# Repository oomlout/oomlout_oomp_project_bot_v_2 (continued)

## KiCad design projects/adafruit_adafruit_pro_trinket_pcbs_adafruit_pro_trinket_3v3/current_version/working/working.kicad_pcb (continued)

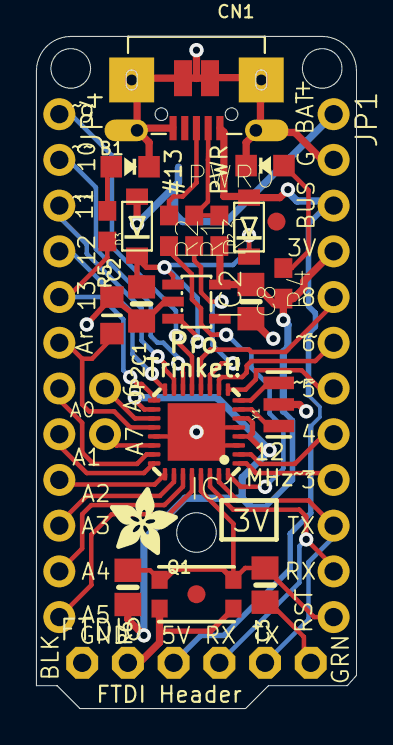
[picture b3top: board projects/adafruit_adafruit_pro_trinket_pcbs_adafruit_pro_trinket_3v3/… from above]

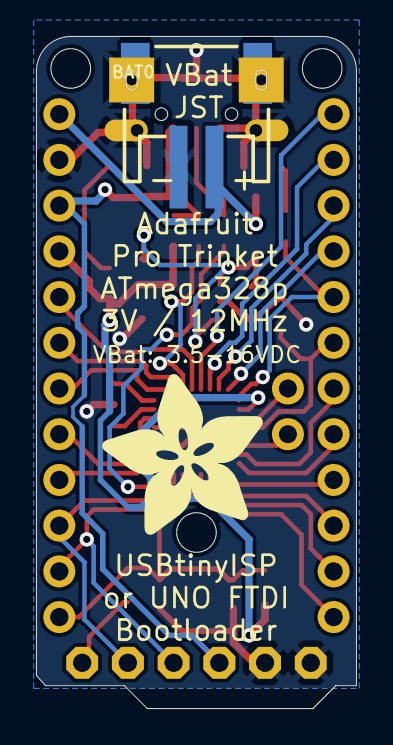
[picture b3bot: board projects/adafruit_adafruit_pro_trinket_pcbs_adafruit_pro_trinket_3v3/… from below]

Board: 16 copper layers, 17.8 x 37.3 mm, 31 parts (2 on the bottom side), 36 nets.

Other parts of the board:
@HOLE0, @HOLE1, @HOLE2: (no value)
U$7: ADAFRUIT_3.5MM
U$9: ADAFRUIT_9MM

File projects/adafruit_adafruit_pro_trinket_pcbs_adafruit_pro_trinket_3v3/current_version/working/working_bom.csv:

"Id";"Designator";"Footprint";"Quantity";"Designation";"Supplier and ref";
1;"IC2";"SOT23-5L";1;"MIC5225-3.3v";;;
2;"D2,D3";"SOD-123FL";2;"SCHOTTKY";;;
3;"JP2";"1X02_ROUND";1;"";;;
4;"@HOLE1,@HOLE2,@HOLE0";"";3;"";;;
5;"IC1";"MLF32-TH";1;"ATmega328P";;;
6;"U$1,U$6";"FIDUCIAL_1MM";2;"FIDUCIAL";;;
7;"C2";"_0805MP";1;"0.1uF";;;
8;"CN1";"4UCONN_20329";1;"";;;
9;"R3";"0603-NO";1;"1.5K (0603)";;;
10;"R4,R5";"0603-NO";2;"470 (0603)";;;
11;"JP4,JP1";"1X12-CB";2;"";;;
12;"Y1";"RESONATOR-SMD";1;"12MHz";;;
13;"U$7";"ADAFRUIT_3.5MM";1;"";;;
14;"C3";"0805-NO";1;"0.1uF";;;
15;"PWR0";"CHIPLED_0805_NOOUTLINE";1;"green";;;
16;"Q1";"BTN_KMR2_4.6X2.8";1;"reset";;;
17;"R1,R2";"0603-NO";2;"68 (0603)";;;
18;"C1,C8";"0805-NO";2;"10uF";;;
19;"B1";"CHIPLED_0805_NOOUTLINE";1;"red";;;
20;"R6";"0805-NO";1;"10K (0603)";;;
21;"FTDI0";"1X06-CLEANBIG";1;"";;;
22;"U$9";"ADAFRUIT_9MM";1;"";;;
23;"BAT0";"JSTPH2";1;"";;;

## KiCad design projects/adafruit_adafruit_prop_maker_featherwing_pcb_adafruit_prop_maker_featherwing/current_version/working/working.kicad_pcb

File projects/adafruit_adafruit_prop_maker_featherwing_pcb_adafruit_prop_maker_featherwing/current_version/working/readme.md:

# adafruit_prop_maker_featherwing_pcb
 
## summary 
* id: adafruit_adafruit_prop_maker_featherwing_pcb_adafruit_prop_maker_featherwing
* user: adafruit
* name: adafruit_prop_maker_featherwing_pcb
* board: adafruit_prop_maker_featherwing
* repo: https://github.com/adafruit/Adafruit-Prop-Maker-FeatherWing-PCB

* src_file_repo_sch: 
* src_file_repo_sch_link: https://github.com/adafruit/Adafruit-Prop-Maker-FeatherWing-PCB/tree/master/
* full details link: https://github.com/oomlout/oomlout_oomp_project_bot_v_2/tree/main/projects/adafruit_adafruit_prop_maker_featherwing_pcb_adafruit_prop_maker_featherwing/current_version/working  

## schematic  
  
[schematic (pdf)](working_schematic.pdf) 

## pcb  

[board (pdf)](working.pdf)  

## working_bom
| Id | Designator | Footprint | Quantity | Designation | Supplier and ref |  | None | 
| --- | --- | --- | --- | --- | --- | --- | --- | 
| 1 | R4,R1,R6,R5 | 0603-NO | 4 | 100k |  |  | [''] | 
| 2 | C1,C15,C2,C3 | 0805-NO | 4 | 10uF |  |  | [''] | 
| 3 | R9,R8 | _1206 | 2 | 1.75o |  |  | [''] | 
| 4 | VR2 | TRIMPOT_BOURNS_3303W | 1 | 10K trim |  |  | [''] | 
| 5 | JP4 | 1X16_ROUND | 1 |  |  |  | [''] | 
| 6 | R2,R3 | 0603-NO | 2 | 10K |  |  | [''] | 
| 7 | R11 | 0603-NO | 1 | 100K |  |  | [''] | 
| 8 | C9,C4,C13 | 0603-NO | 3 | 1uF |  |  | [''] | 
| 9 | FID1,FID3 | FIDUCIAL_1MM | 2 | FIDUCIAL_1MM |  |  | [''] | 
| 10 | Q4,Q2,Q6,Q5 | SOT23-WIDE | 4 | DMG3406 |  |  | [''] | 
| 11 | D2,D1 | SOD-123 | 2 | MBR120 |  |  | [''] | 
| 12 | R12,R13 | 0603-NO | 2 | 100 |  |  | [''] | 
| 13 | U$14 | PROPMAKER_TOP | 1 |  |  |  | [''] | 
| 14 | X6 | JSTPH2 | 1 | CON_JST_PH_2PIN_MTPH2 |  |  | [''] | 
| 15 | @HOLE0,@HOLE2,@HOLE1 |  | 3 |  |  |  | [''] | 
| 16 | NEO0 | JSTPH3 | 1 | JST PH 3 |  |  | [''] | 
| 17 | JP2,EN_PINS0 | 1X02_ROUND | 2 |  |  |  | [''] | 
| 18 | U5 | MSOP8_0.65MM | 1 | PAM8302AASCR |  |  | [''] | 
| 19 | SW1 | BTN_KMR2_4.6X2.8 | 1 | KMR2 |  |  | [''] | 
| 20 | IC4 | LGA16_3X3MM | 1 | LIS3DH |  |  | [''] | 
| 21 | U$1 | 53398-0271 | 1 | CON_MOLEX_2P |  |  | [''] | 
| 22 | JP1 | 1X12_ROUND | 1 |  |  |  | [''] | 
| 23 | IC2 | SOT23-5 | 1 | 74AHCT1G125DBV |  |  | [''] | 
| 24 | R7 | _1206 | 1 | 3o |  |  | [''] | 
| 25 | JP5 | 1X04_ROUND | 1 |  |  |  | [''] | 
| 26 | MS1 | FEATHERWING | 1 | FEATHERWING |  |  | [''] | 
| 27 | Q3 | SOT23-WIDE | 1 | DMG3415U-7 |  |  | [''] | 
| 28 | U$15 | PCBFEAT-REV-040 | 1 |  |  |  | [''] | 
| 29 | U$6 | PROPMAKER_BOT | 1 |  |  |  | [''] | 

## bom_schematic
| Ref | Qnty | Value | Cmp name | Footprint | Description | Vendor | DNP | 
| --- | --- | --- | --- | --- | --- | --- | --- | 
| C1, C2, C3, C15 | 4 | 10uF | CAP_CERAMIC0805-NOOUTLINE | working:0805-NO |  |  |  | 
| C4, C9, C13 | 3 | 1uF | CAP_CERAMIC0603_NO | working:0603-NO |  |  |  | 
| D1, D2 | 2 | MBR120 | DIODE-SCHOTTKYSOD-123 | working:SOD-123 |  |  |  | 
| EN_PINS0 | 1 | HEADER-1X2ROUND | HEADER-1X2ROUND | working:1X02_ROUND |  |  |  | 
| FID1, FID3 | 2 | FIDUCIAL_1MM | FIDUCIAL_1MM | working:FIDUCIAL_1MM |  |  |  | 
| IC2 | 1 | 741G125DBV | 741G125DBV | working:SOT23-5 |  |  |  | 
| IC4 | 1 | LIS3DH | ACCEL_LIS3DHTR | working:LGA16_3X3MM |  |  |  | 
| JP1 | 1 | HEADER-1X12 | HEADER-1X12 | working:1X12_ROUND |  |  |  | 
| JP2 | 1 | HEADER-1X2ROUND | HEADER-1X2ROUND | working:1X02_ROUND |  |  |  | 
| JP4 | 1 | HEADER-1X16ROUND | HEADER-1X16ROUND | working:1X16_ROUND |  |  |  | 
| JP5 | 1 | HEADER-1X4ROUND | HEADER-1X4ROUND | working:1X04_ROUND |  |  |  | 
| MS1 | 1 | FEATHERWING | FEATHERWING | working:FEATHERWING |  |  |  | 
| NEO0 | 1 | JST PH 3 | CON_JST_PH_3PIN | working:JSTPH3 |  |  |  | 
| Q2, Q4, Q5, Q6 | 4 | DMG3406 | MOSFET-NWIDE | working:SOT23-WIDE |  |  |  | 
| Q3 | 1 | DMG3415U-7 | MOSFET-PWIDE | working:SOT23-WIDE |  |  |  | 
| R1, R4, R5, R6 | 4 | 100k | RESISTOR_0603_NOOUT | working:0603-NO |  |  |  | 
| R2, R3 | 2 | 10K | RESISTOR_0603_NOOUT | working:0603-NO |  |  |  | 
| R7 | 1 | 3o | RESISTOR_1206 | working:_1206 |  |  |  | 
| R8, R9 | 2 | 1.75o | RESISTOR_1206 | working:_1206 |  |  |  | 
| R11 | 1 | 100K | RESISTOR_0603_NOOUT | working:0603-NO |  |  |  | 
| R12, R13 | 2 | 100 | RESISTOR_0603_NOOUT | working:0603-NO |  |  |  | 
| SW1 | 1 | KMR2 | SWITCH_TACT_SMT4.6X2.8 | working:BTN_KMR2_4.6X2.8 |  |  |  | 
| U5 | 1 | PAM8302AASCR | AUDIOAMP_PAM8302A | working:MSOP8_0.65MM |  |  |  | 
| U$1 | 1 | CON_MOLEX_2P | CON_MOLEX_2P | working:53398-0271 |  |  |  | 
| VR2 | 1 | 10K trim | TRIMPOT3303W/X | working:TRIMPOT_BOURNS_3303W |  |  |  | 
| X6 | 1 | CON_JST_PH_2PIN_MTPH2 | CON_JST_PH_2PIN_MTPH2 | working:JSTPH2 |  |  |  |

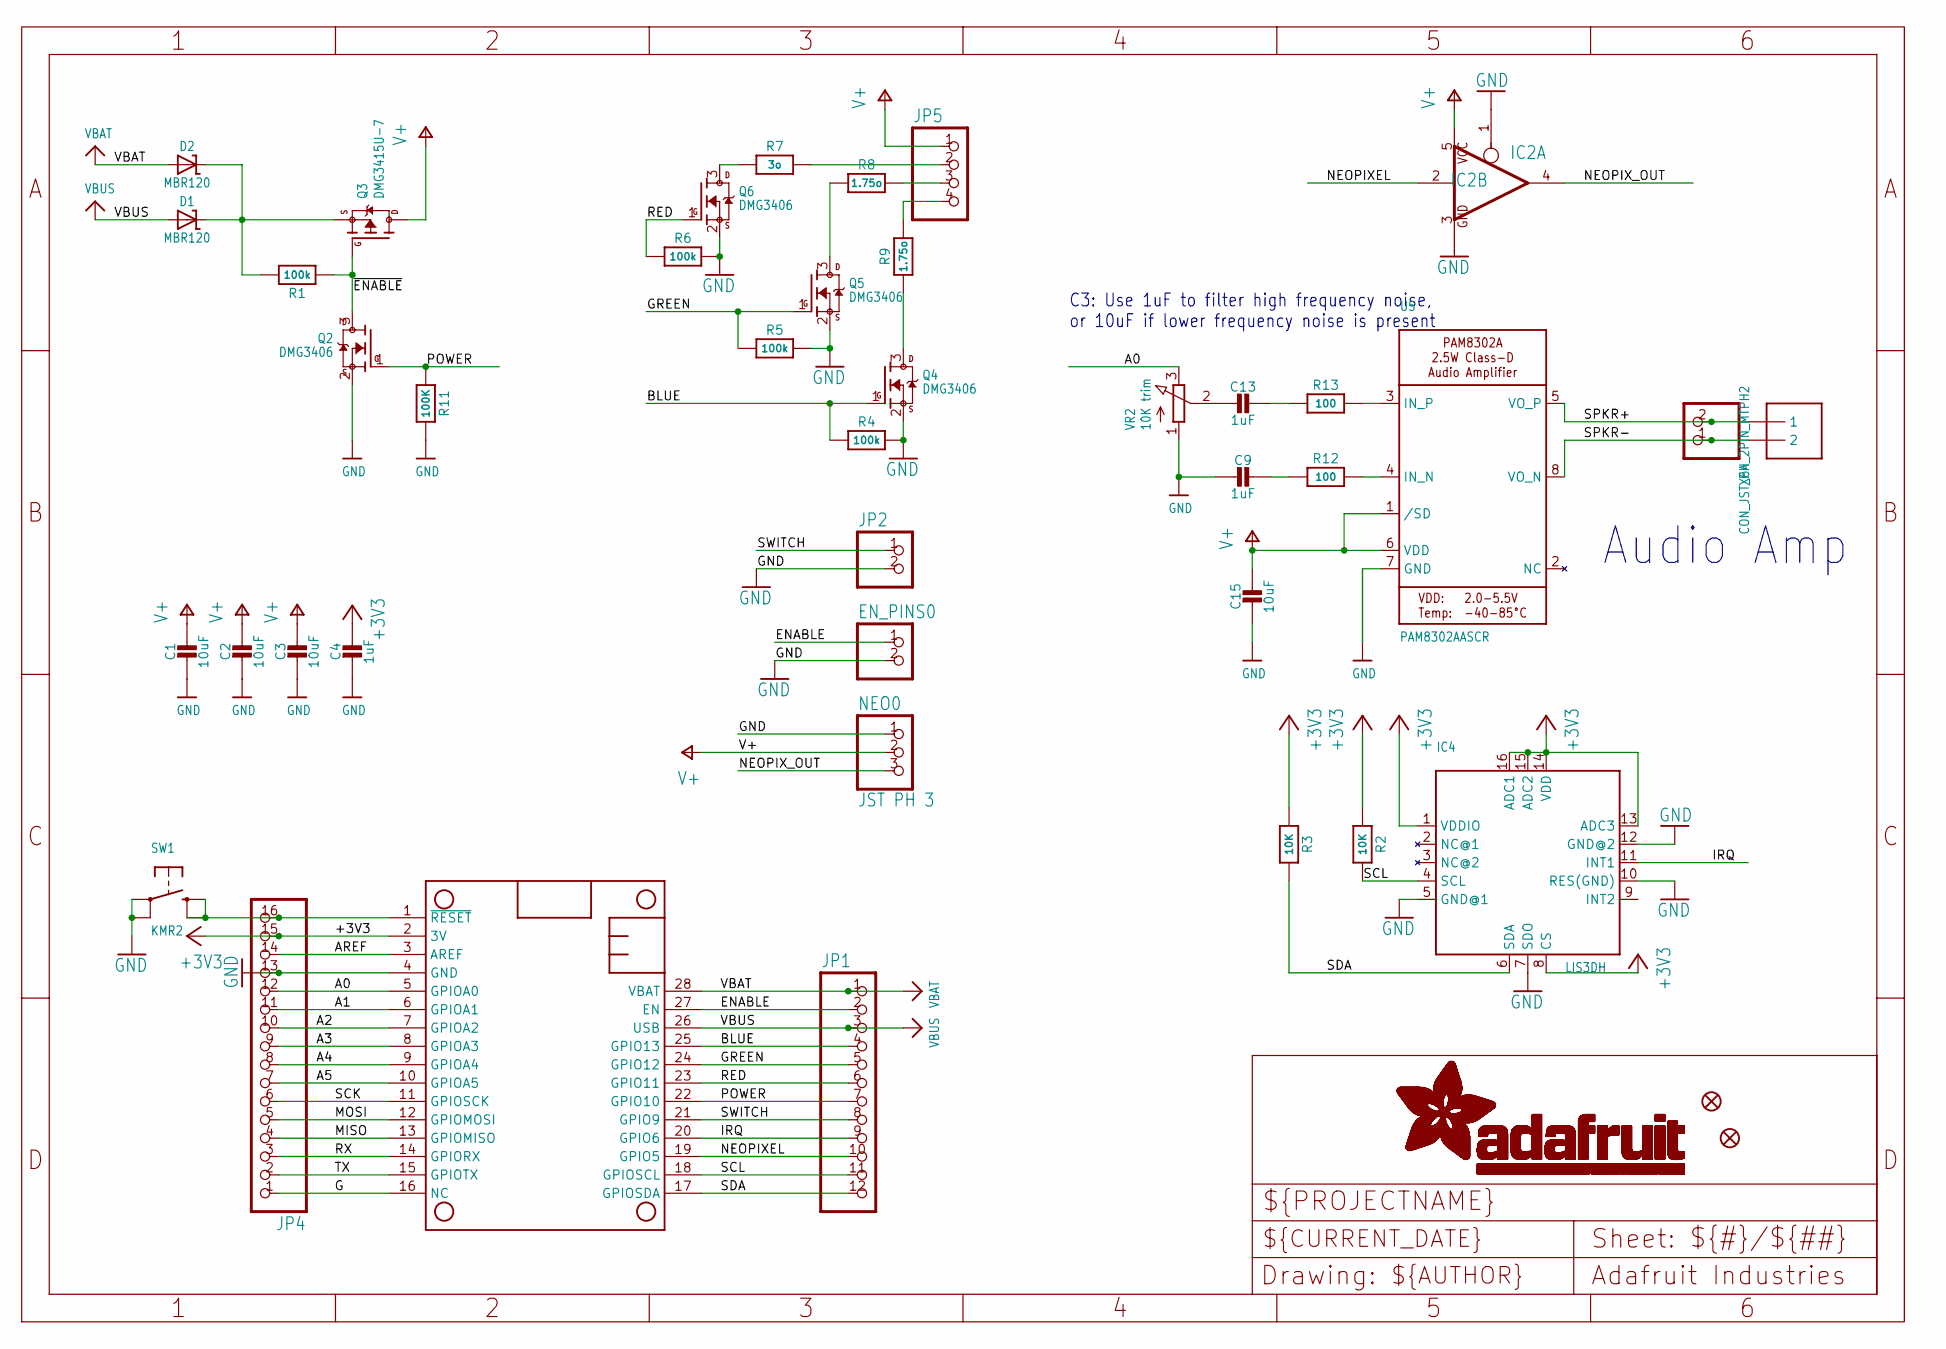
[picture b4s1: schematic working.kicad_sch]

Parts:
C1, C2, C3, C15: 10uF; 0805-NO
C4, C9, C13: 1uF; 0603-NO
D1, D2: MBR120; SOD-123
EN_PINS0: HEADER-1X2ROUND; 1X02_ROUND
FID1, FID3: FIDUCIAL_1MM
IC2: 741G125DBV; SOT23-5
IC4: LIS3DH; LGA16_3X3MM
JP1: HEADER-1X12; 1X12_ROUND
JP2: HEADER-1X2ROUND; 1X02_ROUND
JP4: HEADER-1X16ROUND; 1X16_ROUND
JP5: HEADER-1X4ROUND; 1X04_ROUND
MS1: FEATHERWING
NEO0: JST PH 3; JSTPH3
Q2, Q4, Q5, Q6: DMG3406; SOT23-WIDE
Q3: DMG3415U-7; SOT23-WIDE
R1, R4, R5, R6: 100k; 0603-NO
R2, R3: 10K; 0603-NO
R7: 3o; _1206
R8, R9: 1.75o; _1206
R11: 100K; 0603-NO
R12, R13: 100; 0603-NO
SW1: KMR2; BTN_KMR2_4.6X2.8
U5: PAM8302AASCR; MSOP8_0.65MM
U$1: CON_MOLEX_2P; 53398-0271
VR2: 10K trim; TRIMPOT_BOURNS_3303W
X6: CON_JST_PH_2PIN_MTPH2; JSTPH2

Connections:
+3V3: C4.1, IC4.1 (VDDIO), IC4.8 (CS), IC4.13 (ADC3), IC4.14 (VDD), IC4.15 (ADC2), IC4.16 (ADC1), JP4.15, MS1.2 (3V), R2.1, R3.1
A0: JP4.12, MS1.5 (GPIOA0), VR2.3 (E)
A1: JP4.11, MS1.6 (GPIOA1)
A2: JP4.10, MS1.7 (GPIOA2)
A3: JP4.9, MS1.8 (GPIOA3)
A4: JP4.8, MS1.9 (GPIOA4)
A5: JP4.7, MS1.10 (GPIOA5)
AREF: JP4.14, MS1.3 (AREF)
BLUE: JP1.4, MS1.25 (GPIO13), Q4.1 (G), R4.1
ENABLE: EN_PINS0.1, JP1.2, MS1.27 (EN)
G: JP4.1, MS1.16 (NC)
GND: C1.2, C2.2, C3.2, C4.2, C9.2, C15.2, EN_PINS0.2, IC2.1 (OE), IC2.3 (GND), IC4.5 (GND@1), IC4.7 (SDO), IC4.10 (RES(GND)), IC4.12 (GND@2), JP2.2, JP4.13, MS1.4 (GND), NEO0.1, Q2.2 (S), Q4.2 (S), Q5.2 (S), Q6.2 (S), R4.2, R5.2, R6.2, R11.2, SW1.A, SW1.A' (P1), U5.7 (GND), VR2.1 (A)
GREEN: JP1.5, MS1.24 (GPIO12), Q5.1 (G), R5.1
IRQ: IC4.11 (INT1), JP1.9, MS1.20 (GPIO6)
MISO: JP4.4, MS1.13 (GPIOMISO)
MOSI: JP4.5, MS1.12 (GPIOMOSI)
unnamed: Q6.3 (D), R7.1
unnamed: JP5.3, R8.2
unnamed: JP5.4, R9.2
unnamed: Q4.3 (D), R9.1
unnamed: Q5.3 (D), R8.1
unnamed: JP5.2, R7.2
unnamed: R12.2, U5.4 (IN_N)
unnamed: R13.2, U5.3 (IN_P)
unnamed: C9.1, R12.1
unnamed: C13.1, R13.1
unnamed: C13.2, VR2.2 (S)
unnamed: D1.C, D2.C, Q3.2 (S), R1.2
NEOPIXEL: IC2.2 (I), JP1.10, MS1.19 (GPIO5)
NEOPIX_OUT: IC2.4 (O), NEO0.3
POWER: JP1.7, MS1.22 (GPIO10), Q2.1 (G), R11.1
RED: JP1.6, MS1.23 (GPIO11), Q6.1 (G), R6.1
RESET: JP4.16, MS1.1 (~RESET), SW1.B (S), SW1.B' (S1)
RX: JP4.3, MS1.14 (GPIORX)
SCK: JP4.6, MS1.11 (GPIOSCK)
SCL: IC4.4 (SCL), JP1.11, MS1.18 (GPIOSCL), R2.2
SDA: IC4.6 (SDA), JP1.12, MS1.17 (GPIOSDA), R3.2
SPKR+: U5.5 (VO_P), U$1.1, X6.2
SPKR-: U5.8 (VO_N), U$1.2, X6.1
SWITCH: JP1.8, JP2.1, MS1.21 (GPIO9)
TX: JP4.2, MS1.15 (GPIOTX)
V+: C1.1, C2.1, C3.1, C15.1, IC2.5 (VCC), JP5.1, NEO0.2, Q3.3 (D), U5.1 (/SD), U5.6 (VDD)
VBAT: D2.A, JP1.1, MS1.28 (VBAT)
VBUS: D1.A, JP1.3, MS1.26 (USB)
~ENABLE: Q2.3 (D), Q3.1 (G), R1.1

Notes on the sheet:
C3: Use 1uF to filter high frequency noise, or 10uF if lower frequency noise is present
Audio Amp

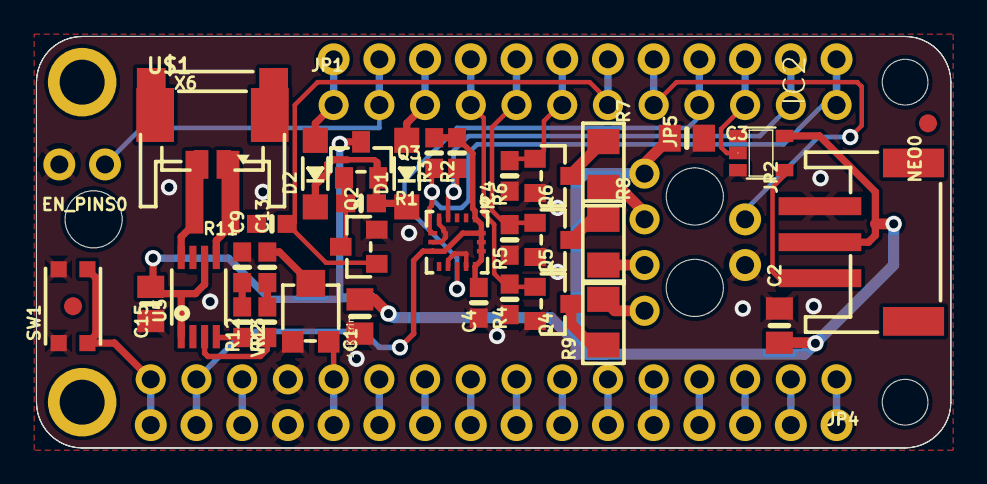
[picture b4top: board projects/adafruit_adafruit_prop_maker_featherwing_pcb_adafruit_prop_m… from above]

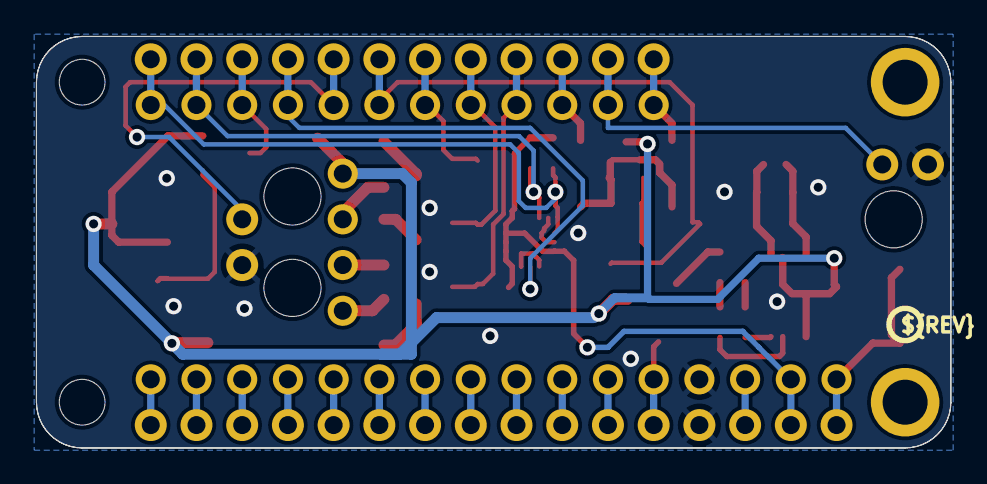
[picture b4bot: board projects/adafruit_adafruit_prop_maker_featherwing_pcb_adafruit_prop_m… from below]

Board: 2 copper layers, 50.8 x 22.9 mm, 48 parts (2 on the bottom side), 45 nets.

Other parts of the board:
@HOLE0, @HOLE1, @HOLE2: (no value)
U$6: PROPMAKER_BOT
U$14: PROPMAKER_TOP
U$15: PCBFEAT-REV-040

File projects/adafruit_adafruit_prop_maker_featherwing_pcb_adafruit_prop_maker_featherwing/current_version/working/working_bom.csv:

"Id";"Designator";"Footprint";"Quantity";"Designation";"Supplier and ref";
1;"R4,R1,R6,R5";"0603-NO";4;"100k";;;
2;"C1,C15,C2,C3";"0805-NO";4;"10uF";;;
3;"R9,R8";"_1206";2;"1.75o";;;
4;"VR2";"TRIMPOT_BOURNS_3303W";1;"10K trim";;;
5;"JP4";"1X16_ROUND";1;"";;;
6;"R2,R3";"0603-NO";2;"10K";;;
7;"R11";"0603-NO";1;"100K";;;
8;"C9,C4,C13";"0603-NO";3;"1uF";;;
9;"FID1,FID3";"FIDUCIAL_1MM";2;"FIDUCIAL_1MM";;;
10;"Q4,Q2,Q6,Q5";"SOT23-WIDE";4;"DMG3406";;;
11;"D2,D1";"SOD-123";2;"MBR120";;;
12;"R12,R13";"0603-NO";2;"100";;;
13;"U$14";"PROPMAKER_TOP";1;"";;;
14;"X6";"JSTPH2";1;"CON_JST_PH_2PIN_MTPH2";;;
15;"@HOLE0,@HOLE2,@HOLE1";"";3;"";;;
16;"NEO0";"JSTPH3";1;"JST PH 3";;;
17;"JP2,EN_PINS0";"1X02_ROUND";2;"";;;
18;"U5";"MSOP8_0.65MM";1;"PAM8302AASCR";;;
19;"SW1";"BTN_KMR2_4.6X2.8";1;"KMR2";;;
20;"IC4";"LGA16_3X3MM";1;"LIS3DH";;;
21;"U$1";"53398-0271";1;"CON_MOLEX_2P";;;
22;"JP1";"1X12_ROUND";1;"";;;
23;"IC2";"SOT23-5";1;"74AHCT1G125DBV";;;
24;"R7";"_1206";1;"3o";;;
25;"JP5";"1X04_ROUND";1;"";;;
26;"MS1";"FEATHERWING";1;"FEATHERWING";;;
27;"Q3";"SOT23-WIDE";1;"DMG3415U-7";;;
28;"U$15";"PCBFEAT-REV-040";1;"";;;
29;"U$6";"PROPMAKER_BOT";1;"";;;

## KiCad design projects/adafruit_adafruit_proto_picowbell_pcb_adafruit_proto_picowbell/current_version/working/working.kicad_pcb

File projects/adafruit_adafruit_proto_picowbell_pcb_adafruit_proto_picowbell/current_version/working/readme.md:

# adafruit_proto_picowbell_pcb
 
## summary 
* id: adafruit_adafruit_proto_picowbell_pcb_adafruit_proto_picowbell
* user: adafruit
* name: adafruit_proto_picowbell_pcb
* board: adafruit_proto_picowbell
* repo: https://github.com/adafruit/Adafruit-Proto-PiCowbell-PCB

* src_file_repo_sch: 
* src_file_repo_sch_link: https://github.com/adafruit/Adafruit-Proto-PiCowbell-PCB/tree/main/
* full details link: https://github.com/oomlout/oomlout_oomp_project_bot_v_2/tree/main/projects/adafruit_adafruit_proto_picowbell_pcb_adafruit_proto_picowbell/current_version/working  

## schematic  
  
[schematic (pdf)](working_schematic.pdf) 

## pcb  

[board (pdf)](working.pdf)  

## working_bom
| Id | Designator | Footprint | Quantity | Designation | Supplier and ref |  | None | 
| --- | --- | --- | --- | --- | --- | --- | --- | 
| 1 | PLABEL34 | PLABEL34 | 1 |  |  |  | [''] | 
| 2 | PLABEL18 | PLABEL18 | 1 |  |  |  | [''] | 
| 3 | PLABEL20 | PLABEL20 | 1 |  |  |  | [''] | 
| 4 | PLABEL4 | PLABEL4 | 1 |  |  |  | [''] | 
| 5 | PLABEL32 | PLABEL32 | 1 |  |  |  | [''] | 
| 6 | PLABEL17 | PLABEL17 | 1 |  |  |  | [''] | 
| 7 | CB1 | PICOWBELL | 1 | PICOWBELL_THM |  |  | [''] | 
| 8 | SW1 | SPST_TACTILE_RA | 1 | RA Tact |  |  | [''] | 
| 9 | JP1,JP2 | 1X20_ROUND_70MIL | 2 |  |  |  | [''] | 
| 10 | PLABEL1 | PLABEL1 | 1 |  |  |  | [''] | 
| 11 | PLABEL16 | PLABEL16 | 1 |  |  |  | [''] | 
| 12 | PLABEL5 | PLABEL5 | 1 |  |  |  | [''] | 
| 13 | PLABEL9 | PLABEL9 | 1 |  |  |  | [''] | 
| 14 | PLABEL15 | PLABEL15 | 1 |  |  |  | [''] | 
| 15 | PLABEL27 | PLABEL27 | 1 |  |  |  | [''] | 
| 16 | PLABEL3 | PLABEL3 | 1 |  |  |  | [''] | 
| 17 | PLABEL10 | PLABEL10 | 1 |  |  |  | [''] | 
| 18 | PLABEL25 | PLABEL25 | 1 |  |  |  | [''] | 
| 19 | FID2,FID1 | FIDUCIAL_1MM | 2 | FIDUCIAL_1MM |  |  | [''] | 
| 20 | PLABEL26 | PLABEL26 | 1 |  |  |  | [''] | 
| 21 | PLABEL23 | PLABEL23 | 1 |  |  |  | [''] | 
| 22 | PLABEL2 | PLABEL2 | 1 |  |  |  | [''] | 
| 23 | PLABEL33 | PLABEL33 | 1 |  |  |  | [''] | 
| 24 | PLABEL30 | PLABEL30 | 1 |  |  |  | [''] | 
| 25 | PLABEL28 | PLABEL28 | 1 |  |  |  | [''] | 
| 26 | PLABEL29 | PLABEL29 | 1 |  |  |  | [''] | 
| 27 | PLABEL13 | PLABEL13 | 1 |  |  |  | [''] | 
| 28 | PLABEL12 | PLABEL12 | 1 |  |  |  | [''] | 
| 29 | PLABEL8 | PLABEL8 | 1 |  |  |  | [''] | 
| 30 | PLABEL0 | PLABEL0 | 1 |  |  |  | [''] | 
| 31 | CONN1 | JST_SH4 | 1 | STEMMA_I2C_QT |  |  | [''] | 
| 32 | PLABEL11 | PLABEL11 | 1 |  |  |  | [''] | 
| 33 | PLABEL21 | PLABEL21 | 1 |  |  |  | [''] | 
| 34 | PLABEL31 | PLABEL31 | 1 |  |  |  | [''] | 
| 35 | PLABEL22 | PLABEL22 | 1 |  |  |  | [''] | 
| 36 | PLABEL24 | PLABEL24 | 1 |  |  |  | [''] | 
| 37 | PLABEL7 | PLABEL7 | 1 |  |  |  | [''] | 
| 38 | PLABEL14 | PLABEL14 | 1 |  |  |  | [''] | 
| 39 | PLABEL19 | PLABEL19 | 1 |  |  |  | [''] | 
| 40 | PLABEL6 | PLABEL6 | 1 |  |  |  | [''] | 
| 41 | PLABEL64 | PLABEL64 | 1 |  |  |  | [''] | 
| 42 | PLABEL38 | PLABEL38 | 1 |  |  |  | [''] | 
| 43 | PLABEL51 | PLABEL51 | 1 |  |  |  | [''] | 
| 44 | PLABEL58 | PLABEL58 | 1 |  |  |  | [''] | 
| 45 | PLABEL46 | PLABEL46 | 1 |  |  |  | [''] | 
| 46 | PLABEL49 | PLABEL49 | 1 |  |  |  | [''] | 
| 47 | PLABEL67 | PLABEL67 | 1 |  |  |  | [''] | 
| 48 | PLABEL39 | PLABEL39 | 1 |  |  |  | [''] | 
| 49 | PLABEL65 | PLABEL65 | 1 |  |  |  | [''] | 
| 50 | PLABEL62 | PLABEL62 | 1 |  |  |  | [''] | 
| 51 | PLABEL63 | PLABEL63 | 1 |  |  |  | [''] | 
| 52 | PLABEL36 | PLABEL36 | 1 |  |  |  | [''] | 
| 53 | PLABEL45 | PLABEL45 | 1 |  |  |  | [''] | 
| 54 | PLABEL53 | PLABEL53 | 1 |  |  |  | [''] | 
| 55 | PLABEL52 | PLABEL52 | 1 |  |  |  | [''] | 
| 56 | U$2 | ADAFRUIT_2.5MM | 1 |  |  |  | [''] | 
| 57 | PLABEL55 | PLABEL55 | 1 |  |  |  | [''] | 
| 58 | PLABEL50 | PLABEL50 | 1 |  |  |  | [''] | 
| 59 | U$6 | PCBFEAT-REV-040 | 1 |  |  |  | [''] | 
| 60 | PLABEL41 | PLABEL41 | 1 |  |  |  | [''] | 
| 61 | PLABEL47 | PLABEL47 | 1 |  |  |  | [''] | 
| 62 | PLABEL40 | PLABEL40 | 1 |  |  |  | [''] | 
| 63 | PLABEL61 | PLABEL61 | 1 |  |  |  | [''] | 
| 64 | PLABEL60 | PLABEL60 | 1 |  |  |  | [''] | 
| 65 | PLABEL54 | PLABEL54 | 1 |  |  |  | [''] | 
| 66 | PLABEL59 | PLABEL59 | 1 |  |  |  | [''] | 
| 67 | PLABEL43 | PLABEL43 | 1 |  |  |  | [''] | 
| 68 | PLABEL57 | PLABEL57 | 1 |  |  |  | [''] | 
| 69 | PLABEL44 | PLABEL44 | 1 |  |  |  | [''] | 
| 70 | PLABEL48 | PLABEL48 | 1 |  |  |  | [''] | 
| 71 | PLABEL37 | PLABEL37 | 1 |  |  |  | [''] | 
| 72 | PLABEL42 | PLABEL42 | 1 |  |  |  | [''] | 
| 73 | PLABEL56 | PLABEL56 | 1 |  |  |  | [''] | 
| 74 | PLABEL35 | PLABEL35 | 1 |  |  |  | [''] | 
| 75 | PLABEL66 | PLABEL66 | 1 |  |  |  | [''] | 

## bom_schematic
| Ref | Qnty | Value | Cmp name | Footprint | Description | Vendor | DNP | 
| --- | --- | --- | --- | --- | --- | --- | --- | 
| CB1 | 1 | PICOWBELL_THM | PICOWBELL_THM | working:PICOWBELL |  |  |  | 
| CONN1 | 1 | STEMMA_I2C_QT | STEMMA_I2C_QT | working:JST_SH4 |  |  |  | 
| FID1, FID2 | 2 | FIDUCIAL_1MM | FIDUCIAL_1MM | working:FIDUCIAL_1MM |  |  |  | 
| JP1, JP2 | 2 | HEADER-1X20_70MIL | HEADER-1X20_70MIL | working:1X20_ROUND_70MIL |  |  |  | 
| SW1 | 1 | RA Tact | SWITCH_SPST_MNT_TACT_RA | working:SPST_TACTILE_RA |  |  |  |

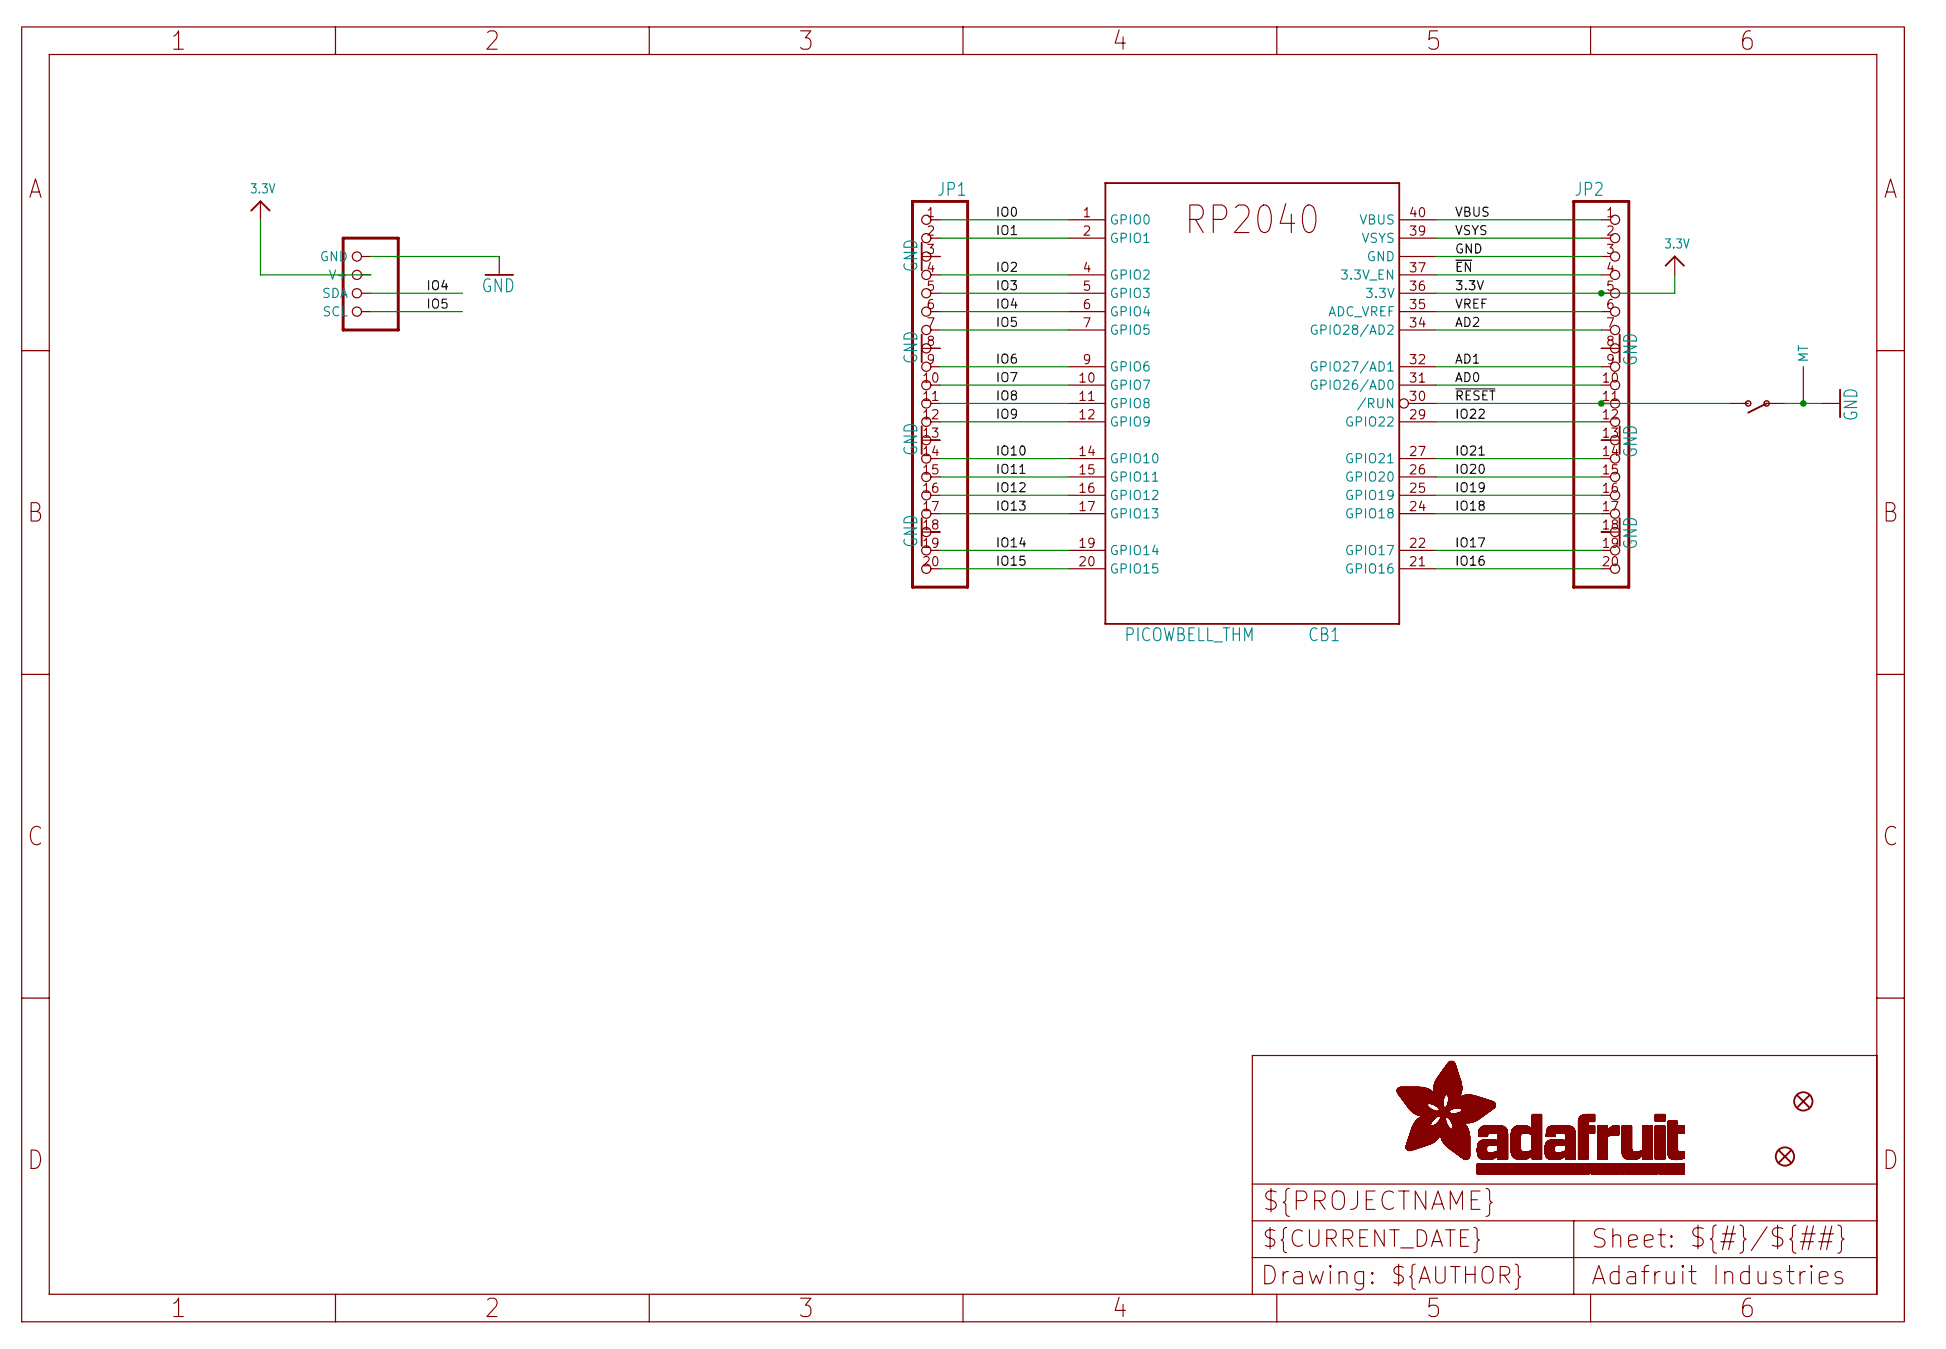
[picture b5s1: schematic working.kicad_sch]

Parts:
CB1: PICOWBELL_THM; PICOWBELL
CONN1: STEMMA_I2C_QT; JST_SH4
FID1, FID2: FIDUCIAL_1MM
JP1, JP2: HEADER-1X20_70MIL; 1X20_ROUND_70MIL
SW1: RA Tact; SPST_TACTILE_RA

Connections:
3.3V: CB1.36 (3.3V), CONN1.2 (V+), JP2.5
AD0: CB1.31 (GPIO26/AD0), JP2.10
AD1: CB1.32 (GPIO27/AD1), JP2.9
AD2: CB1.34 (GPIO28/AD2), JP2.7
GND: CB1.3 (GND), CB1.8 (GND), CB1.13 (GND), CB1.18 (GND), CB1.23 (GND), CB1.28 (GND), CB1.33 (GND), CB1.38 (GND), CONN1.1 (GND), JP1.3, JP1.8, JP1.13, JP1.18, JP2.3, JP2.8, JP2.13, JP2.18, SW1.1, SW1.MT1 (MT), SW1.MT2 (MT)
IO0: CB1.1 (GPIO0), JP1.1
IO1: CB1.2 (GPIO1), JP1.2
IO2: CB1.4 (GPIO2), JP1.4
IO3: CB1.5 (GPIO3), JP1.5
IO4: CB1.6 (GPIO4), CONN1.3 (SDA), JP1.6
IO5: CB1.7 (GPIO5), CONN1.4 (SCL), JP1.7
IO6: CB1.9 (GPIO6), JP1.9
IO7: CB1.10 (GPIO7), JP1.10
IO8: CB1.11 (GPIO8), JP1.11
IO9: CB1.12 (GPIO9), JP1.12
IO10: CB1.14 (GPIO10), JP1.14
IO11: CB1.15 (GPIO11), JP1.15
IO12: CB1.16 (GPIO12), JP1.16
IO13: CB1.17 (GPIO13), JP1.17
IO14: CB1.19 (GPIO14), JP1.19
IO15: CB1.20 (GPIO15), JP1.20
IO16: CB1.21 (GPIO16), JP2.20
IO17: CB1.22 (GPIO17), JP2.19
IO18: CB1.24 (GPIO18), JP2.17
IO19: CB1.25 (GPIO19), JP2.16
IO20: CB1.26 (GPIO20), JP2.15
IO21: CB1.27 (GPIO21), JP2.14
IO22: CB1.29 (GPIO22), JP2.12
VBUS: CB1.40 (VBUS), JP2.1
VREF: CB1.35 (ADC_VREF), JP2.6
VSYS: CB1.39 (VSYS), JP2.2
~EN: CB1.37 (3.3V_EN), JP2.4
~RESET: CB1.30 (/RUN), JP2.11, SW1.2 (S)

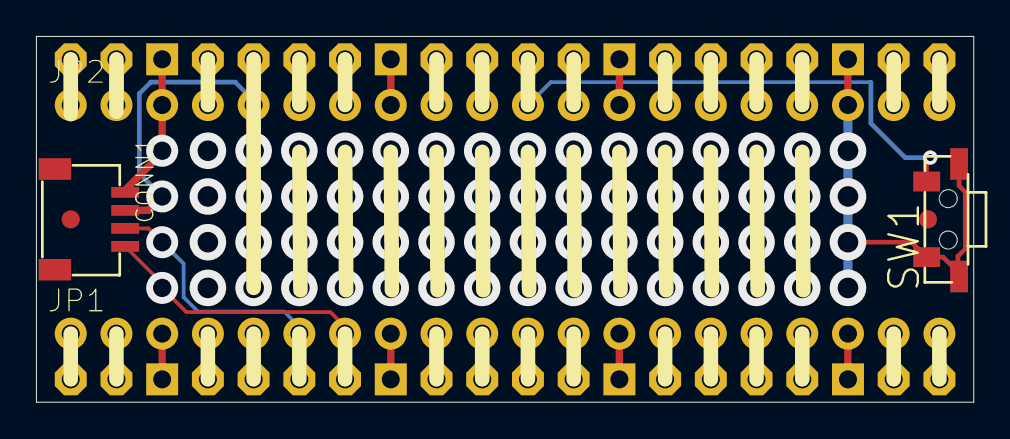
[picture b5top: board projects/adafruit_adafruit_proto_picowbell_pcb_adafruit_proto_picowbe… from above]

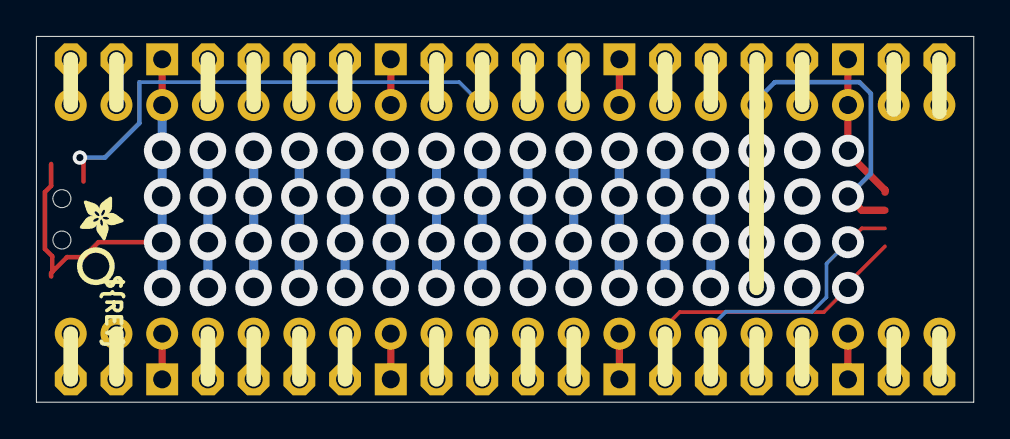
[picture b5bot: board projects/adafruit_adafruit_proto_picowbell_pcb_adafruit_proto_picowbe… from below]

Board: 2 copper layers, 52.1 x 20.3 mm, 77 parts (35 on the bottom side), 33 nets.

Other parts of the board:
PLABEL0: PLABEL0
PLABEL1: PLABEL1
PLABEL2: PLABEL2
PLABEL3: PLABEL3
PLABEL4: PLABEL4
PLABEL5: PLABEL5
PLABEL6: PLABEL6
PLABEL7: PLABEL7
PLABEL8: PLABEL8
PLABEL9: PLABEL9
PLABEL10: PLABEL10
PLABEL11: PLABEL11
PLABEL12: PLABEL12
PLABEL13: PLABEL13
PLABEL14: PLABEL14
PLABEL15: PLABEL15
PLABEL16: PLABEL16
PLABEL17: PLABEL17
PLABEL18: PLABEL18
PLABEL19: PLABEL19
PLABEL20: PLABEL20
PLABEL21: PLABEL21
PLABEL22: PLABEL22
PLABEL23: PLABEL23
PLABEL24: PLABEL24
PLABEL25: PLABEL25
PLABEL26: PLABEL26
PLABEL27: PLABEL27
PLABEL28: PLABEL28
PLABEL29: PLABEL29
PLABEL30: PLABEL30
PLABEL31: PLABEL31
PLABEL32: PLABEL32
PLABEL33: PLABEL33
PLABEL34: PLABEL34
PLABEL35: PLABEL35
PLABEL36: PLABEL36
PLABEL37: PLABEL37
PLABEL38: PLABEL38
PLABEL39: PLABEL39
PLABEL40: PLABEL40
PLABEL41: PLABEL41
PLABEL42: PLABEL42
PLABEL43: PLABEL43
PLABEL44: PLABEL44
PLABEL45: PLABEL45
PLABEL46: PLABEL46
PLABEL47: PLABEL47
PLABEL48: PLABEL48
PLABEL49: PLABEL49
PLABEL50: PLABEL50
PLABEL51: PLABEL51
PLABEL52: PLABEL52
PLABEL53: PLABEL53
PLABEL54: PLABEL54
PLABEL55: PLABEL55
PLABEL56: PLABEL56
PLABEL57: PLABEL57
PLABEL58: PLABEL58
PLABEL59: PLABEL59
PLABEL60: PLABEL60
PLABEL61: PLABEL61
PLABEL62: PLABEL62
PLABEL63: PLABEL63
PLABEL64: PLABEL64
PLABEL65: PLABEL65
PLABEL66: PLABEL66
PLABEL67: PLABEL67
U$2: ADAFRUIT_2.5MM
U$6: PCBFEAT-REV-040

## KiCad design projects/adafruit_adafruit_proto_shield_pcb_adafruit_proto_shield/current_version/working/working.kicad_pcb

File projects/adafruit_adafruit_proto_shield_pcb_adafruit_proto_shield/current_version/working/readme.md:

# adafruit_proto_shield_pcb
 
## summary 
* id: adafruit_adafruit_proto_shield_pcb_adafruit_proto_shield
* user: adafruit
* name: adafruit_proto_shield_pcb
* board: adafruit_proto_shield
* repo: https://github.com/adafruit/Adafruit-Proto-Shield-PCB

* src_file_repo_sch: 
* src_file_repo_sch_link: https://github.com/adafruit/Adafruit-Proto-Shield-PCB/tree/master/
* full details link: https://github.com/oomlout/oomlout_oomp_project_bot_v_2/tree/main/projects/adafruit_adafruit_proto_shield_pcb_adafruit_proto_shield/current_version/working  

## schematic  
  
[schematic (pdf)](working_schematic.pdf) 

## pcb  

[board (pdf)](working.pdf)  

## working_bom
| Id | Designator | Footprint | Quantity | Designation | Supplier and ref |  | None | 
| --- | --- | --- | --- | --- | --- | --- | --- | 
| 1 | U$6,U$35,U$7,U$4,U$19,U$34,U$16,U$8,U$39,U$25,U$38,U$2,U$41,U$37,U$40,U$27,U$9 | PERFHOLE | 17 | PERFHOLE |  |  | [''] | 
| 2 | U$1 | 1X10-BIG | 1 | PINHD-1X10 |  |  | [''] | 
| 3 | U$11,U$23,U$33,U$21,U$28,U$15,U$29,U$32,U$26,U$17,U$31,U$18,U$20,U$13,U$30,U$12,U$14,U$10,U$5,U$22 | 3-STRIP | 20 | 3-STRIP |  |  | [''] | 
| 4 | JP1,JP4 | 1X08-BIG | 2 |  |  |  | [''] | 
| 5 | C2,C1 | C025-025X050 | 2 |  |  |  | [''] | 
| 6 | @HOLE1,@HOLE0 |  | 2 |  |  |  | [''] | 
| 7 | JP9 | 1X06-BIG | 1 |  |  |  | [''] | 
| 8 | U$43,U$24,U$3 | 5-STRIP | 3 | 5-STRIP |  |  | [''] | 
| 9 | LED1,LED2 | LED3MM | 2 |  |  |  | [''] | 
| 10 | R2,R1 | 0207_5V | 2 |  |  |  | [''] | 
| 11 | M1 | ARDUINOR3_ICSP | 1 | ARDUINO_R3_ICSP |  |  | [''] | 
| 12 | S1,RESET0 | B3F-10XX | 2 | Reset |  |  | [''] | 
| 13 | IC1 | SO-14NMW | 1 | SMD-14 |  |  | [''] | 
| 14 | VCCSTRIP1,GNDSTRIP2,VCCSTRIP2,GNDSTRIP1 | 12-STRIP | 4 | 12-STRIP |  |  | [''] | 
| 15 | U$36 | ADAFRUIT_9MM | 1 |  |  |  | [''] | 

## bom_schematic
| Ref | Qnty | Value | Cmp name | Footprint | Description | Vendor | DNP | 
| --- | --- | --- | --- | --- | --- | --- | --- | 
| C1, C2 | 2 | C-US025-025X050 | C-US025-025X050 | working:C025-025X050 |  |  |  | 
| GNDSTRIP1, GNDSTRIP2 | 2 | 12-STRIP | 12-STRIP | working:12-STRIP |  |  |  | 
| IC1 | 1 | SMD-14 | SMD-14 | working:SO-14NMW |  |  |  | 
| JP1, JP4 | 2 | PINHD-1X8BIG | PINHD-1X8BIG | working:1X08-BIG |  |  |  | 
| JP9 | 1 | PINHD-1X6B | PINHD-1X6B | working:1X06-BIG |  |  |  | 
| LED1, LED2 | 2 | LED3MM | LED3MM | working:LED3MM |  |  |  | 
| M1 | 1 | ARDUINO_R3_ICSP | ARDUINO_R3_ICSP | working:ARDUINOR3_ICSP |  |  |  | 
| R1, R2 | 2 | R-US_0207/5V | R-US_0207/5V | working:0207_5V |  |  |  | 
| RESET0 | 1 | Reset | 10-XX | working:B3F-10XX |  |  |  | 
| S1 | 1 | Reset | 10-XX | working:B3F-10XX |  |  |  | 
| U$1 | 1 | PINHD-1X10 | PINHD-1X10 | working:1X10-BIG |  |  |  | 
| U$2, U$4, U$6, U$7, U$8, U$9, U$16, U$19, U$25, U$27, U$34, U$35, U$37, U$38, U$39, U$40, U$41 | 17 | PERFHOLE | PERFHOLE | working:PERFHOLE |  |  |  | 
| U$3, U$24, U$43 | 3 | 5-STRIP | 5-STRIP | working:5-STRIP |  |  |  | 
| U$5, U$10, U$11, U$12, U$13, U$14, U$15, U$17, U$18, U$20, U$21, U$22, U$23, U$26, U$28, U$29, U$30, U$31, U$32, U$33 | 20 | 3-STRIP | 3-STRIP | working:3-STRIP |  |  |  | 
| VCCSTRIP1, VCCSTRIP2 | 2 | 12-STRIP | 12-STRIP | working:12-STRIP |  |  |  |

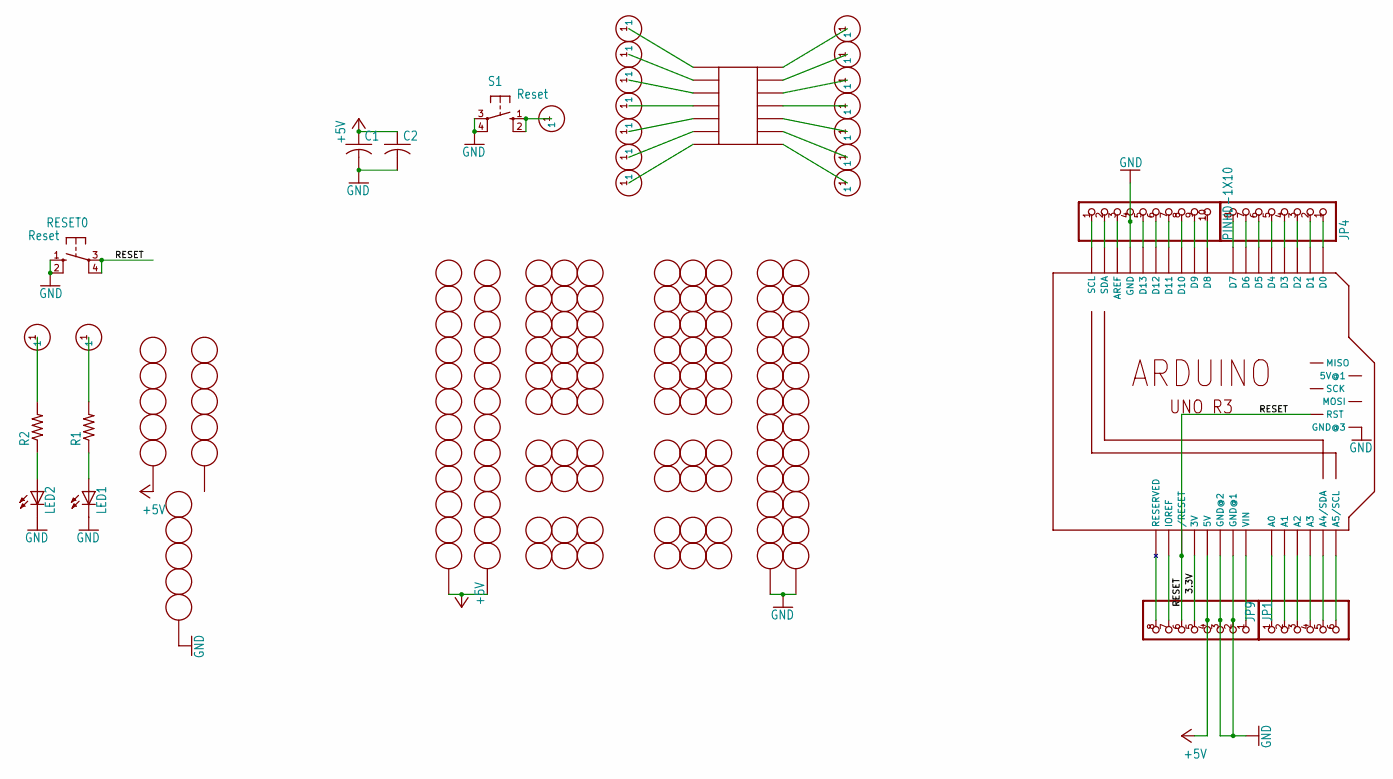
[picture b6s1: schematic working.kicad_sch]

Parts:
C1, C2: C-US025-025X050; C025-025X050
GNDSTRIP1, GNDSTRIP2: 12-STRIP
IC1: SMD-14; SO-14NMW
JP1, JP4: PINHD-1X8BIG; 1X08-BIG
JP9: PINHD-1X6B; 1X06-BIG
LED1, LED2: LED3MM
M1: ARDUINO_R3_ICSP; ARDUINOR3_ICSP
R1, R2: R-US_0207/5V; 0207_5V
RESET0: Reset; B3F-10XX
S1: Reset; B3F-10XX
U$1: PINHD-1X10; 1X10-BIG
U$2, U$4, U$6, U$7, U$8, U$9, U$16, U$19, U$25, U$27, U$34, U$35, U$37, U$38, U$39, U$40, U$41: PERFHOLE
U$3, U$24, U$43: 5-STRIP
U$5, U$10, U$11, U$12, U$13, U$14, U$15, U$17, U$18, U$20, U$21, U$22, U$23, U$26, U$28, U$29, U$30, U$31, U$32, U$33: 3-STRIP
VCCSTRIP1, VCCSTRIP2: 12-STRIP

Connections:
3.3V: JP1.5, M1.3V
+5V: C1.1, C2.1, JP1.4, M1.5V, U$24.P$3, VCCSTRIP1.P$1, VCCSTRIP2.P$1
GND: C1.2, C2.2, GNDSTRIP1.P$1, GNDSTRIP2.P$1, JP1.2, JP1.3, LED1.K (C), LED2.K (C), M1.GND, M1.GND@1 (GND@2), M1.GND@2 (GND@3), M1.GND@3 (GND@1), RESET0.1 (S), RESET0.2 (S1), S1.3, S1.4 (P1), U$1.4, U$43.P$3
unnamed: M1.AREF, U$1.3
unnamed: JP1.8, M1.RESERVED
unnamed: M1.D13, U$1.5
unnamed: LED1.A, R1.1
unnamed: JP1.7, M1.IOREF
unnamed: R1.2, U$7.1
unnamed: R2.2, U$4.1
unnamed: LED2.A, R2.1
unnamed: M1.D12, U$1.6
unnamed: M1.D11, U$1.7
unnamed: M1.D10, U$1.8
unnamed: M1.D9, U$1.9
unnamed: M1.D8, U$1.10
unnamed: JP9.1, M1.A0
unnamed: JP9.2, M1.A1
unnamed: JP9.3, M1.A2
unnamed: JP9.4, M1.A3
unnamed: JP9.5, M1.A4 (A4/SDA)
unnamed: JP9.6, M1.A5 (A5/SCL)
unnamed: JP4.1, M1.D0
unnamed: JP4.2, M1.D1
unnamed: JP4.3, M1.D2
unnamed: JP4.4, M1.D3
unnamed: JP4.5, M1.D4
unnamed: IC1.P$1, U$2.1
unnamed: IC1.P$2, U$6.1
unnamed: JP4.6, M1.D5
unnamed: JP4.7, M1.D6
unnamed: IC1.P$3, U$8.1
unnamed: IC1.P$4, U$9.1
unnamed: IC1.P$5, U$19.1
unnamed: JP4.8, M1.D7
unnamed: JP1.1, M1.VIN
unnamed: M1.SCL, U$1.1
unnamed: IC1.P$6, U$25.1
unnamed: IC1.P$7, U$27.1
unnamed: IC1.P$8, U$34.1
unnamed: IC1.P$9, U$35.1
unnamed: IC1.P$10, U$37.1
unnamed: M1.SDA, U$1.2
unnamed: IC1.P$11, U$38.1
unnamed: IC1.P$12, U$39.1
unnamed: IC1.P$13, U$40.1
unnamed: IC1.P$14, U$41.1
unnamed: S1.1 (S), S1.2 (S1), U$16.1
RESET: JP1.6, M1.RESET (/RESET), M1.RESET_ICSP (RST), RESET0.3, RESET0.4 (P1)

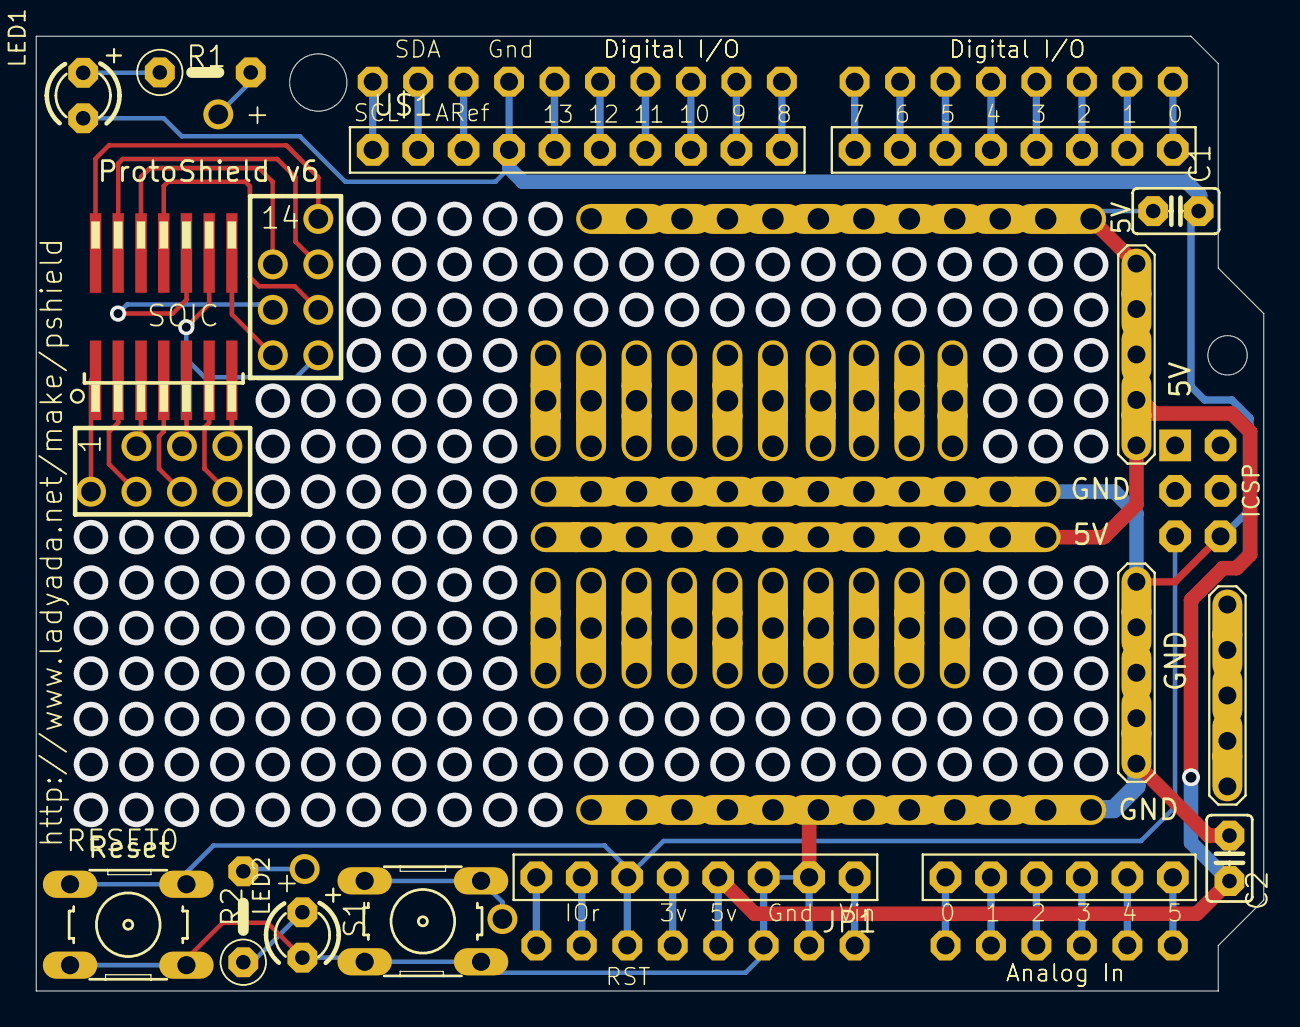
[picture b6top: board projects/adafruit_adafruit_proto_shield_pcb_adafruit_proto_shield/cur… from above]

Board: 2 copper layers, 68.6 x 53.3 mm, 61 parts (1 on the bottom side), 49 nets.

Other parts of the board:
@HOLE0, @HOLE1: (no value)
U$36: ADAFRUIT_9MM
